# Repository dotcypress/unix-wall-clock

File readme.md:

# unix-wall-clock

<sub>Banana for scale</sub>

## License

Licensed under either of

- Apache License, Version 2.0 ([LICENSE-APACHE](LICENSE-APACHE) or
  http://www.apache.org/licenses/LICENSE-2.0)
- MIT license ([LICENSE-MIT](LICENSE-MIT) or http://opensource.org/licenses/MIT)

at your option.

### Contribution

Unless you explicitly state otherwise, any contribution intentionally submitted
for inclusion in the work by you, as defined in the Apache-2.0 license, shall be
dual licensed as above, without any additional terms or conditions.

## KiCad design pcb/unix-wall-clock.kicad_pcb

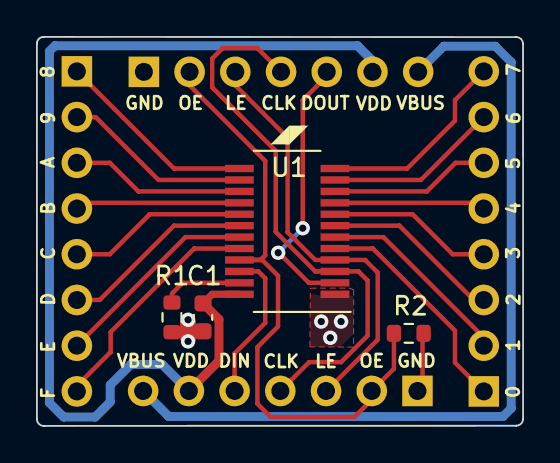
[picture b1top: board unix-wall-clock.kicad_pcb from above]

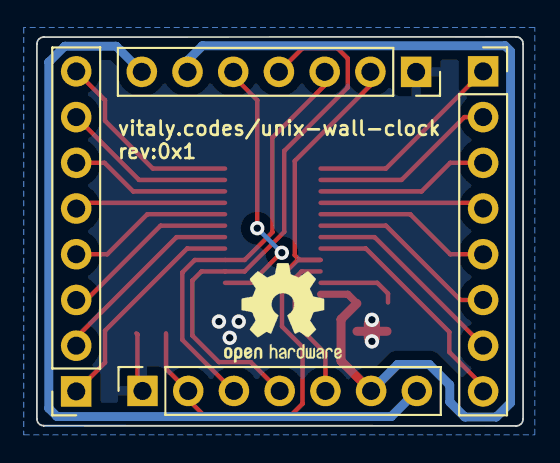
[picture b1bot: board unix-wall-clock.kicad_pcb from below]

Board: 2 copper layers, 27.0 x 21.6 mm, 8 parts (4 on the bottom side), 25 nets.

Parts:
C1: 10uF; C_0603_1608Metric
J1, J2: Conn_01x08_Female; PinSocket_1x08_P2.54mm_Vertical
J3, J4: Conn_01x07_Female; PinSocket_1x07_P2.54mm_Vertical
R1: R_Small; R_0603_1608Metric
R2: NP; R_0603_1608Metric
U1: STP16CP05; QSOP-24_3.9x8.7mm_P0.635mm

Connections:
GND: C1.2, J3.1, J4.1, R1.1, R2.1, U1.1 (GND)
unnamed: J3.5, U1.2 (SDI)
unnamed: J3.4, J4.4, U1.3 (CLK)
unnamed: J3.3, J4.3, U1.4 (LE/DM1)
unnamed: J1.1, U1.5 (~OUT0)
unnamed: J1.2, U1.6 (~OUT1)
unnamed: J1.3, U1.7 (~OUT2)
unnamed: J1.4, U1.8 (~OUT3)
unnamed: J1.5, U1.9 (~OUT4)
unnamed: J1.6, U1.10 (~OUT5)
unnamed: J1.7, U1.11 (~OUT6)
unnamed: J1.8, U1.12 (~OUT7)
unnamed: J2.1, U1.13 (~OUT8)
unnamed: J2.2, U1.14 (~OUT9)
unnamed: J2.3, U1.15 (~OUT10)
unnamed: J2.4, U1.16 (~OUT11)
unnamed: J2.5, U1.17 (~OUT12)
unnamed: J2.6, U1.18 (~OUT13)
unnamed: J2.7, U1.19 (~OUT14)
unnamed: J2.8, U1.20 (~OUT15)
unnamed: J3.2, J4.2, R2.2, U1.21 (~OE/DM2)
unnamed: J4.5, U1.22 (SDO)
unnamed: R1.2, U1.23 (R-EXT)
VBUS: J3.7, J4.7
VDD: C1.1, J3.6, J4.6, U1.24 (VDD)

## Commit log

2023-08-08 gps control
2023-08-08 ir commands
2023-08-08 cleanup
2023-08-09 remove animation
2024-06-12 add video
